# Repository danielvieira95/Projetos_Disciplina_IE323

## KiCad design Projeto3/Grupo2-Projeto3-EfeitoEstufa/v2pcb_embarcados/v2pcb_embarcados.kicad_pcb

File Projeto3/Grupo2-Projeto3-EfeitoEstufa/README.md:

# Projeto 3 - Efeito Estufa e Aquecimento Global - IE323A - Tópicos em Eletrônica

## Autor

Victor Anthony Teixeira dos Santos - 206467

## Introdução
Este projeto, se trata de um experimento em que podemos demonstrar o efeito estufa e o aquecimento global, de forma que possamos elucidar esse problema de uma maneira clara para os alunos.

## Objetivos
A ideia é que os professores possam usar a BitDogLab para complementar o que foi passado em aula, de forma que possa facilitar a melhor visualização do aluno sobre o conteúdo a ser estudado.

   Este projeto está alinhado com as seguintes habilidades específicas da BNCC:

**(EF07CI12)** Demonstrar que o ar é uma mistura de gases, identificando sua composição, e discutir fenômenos naturais ou antrópicos que podem alterar essa composição.

**(EF07CI13)** Descrever o mecanismo natural do efeito estufa, seu papel fundamental para o desenvolvimento da vida na Terra, discutir as ações humanas responsáveis pelo seu aumento artificial (queima dos combustíveis fósseis, desmatamento, queimadas etc.) e selecionar e implementar propostas para a reversão ou controle desse quadro.

## Materiais Utilizados:

**Recursos on-board**
- Display Oled
- Botão
- Matriz RGB
- Buzzer

**Recursos off-board**
- 2 x Sensores de Temperatura e Umidade BME680
- 16 x Cabos groove 20cm
- 2 x Conectores para cabo groove
- 1 x Sensor HC05
- 1 x PCB Adaptada para o sensor HC05

## Código

O software foi projetado para ter uma interação entre os sensores BME680 e o HC05, junto com o display OLED, a matriz RGB e o buzzer.
O display OLED mostrará a temperatura, umidade, gás e pressão em cada ambiente. Nessa parte tem uma interação com o botão, que ao pressionar o botão você alterna entre os sensores para ver as respectivas informações. Outra interação que vai ter é com a matriz RGB, de acordo com a temperatura a matriz RGB muda de cor e quando atingir uma temperatura acima de 30°C o buzzer aciona. Um adendo sobre a matriz RGB é que as duas primeiras colunas serão destinadas para o primeiro sensor e as duas últimas serão destinadas ao segundo sensor.
Essas informações são enviadas para o sensor bluetooth HC05, e posteriormente serão lidas por uma dashboard. Dessa forma, será possível ver as informações no celular também.

Abaixo temos dois fluxogramas do código e uma imagem para ilustrar melhor.

Fluxograma 1

Fluxograma 2

Exemplo BitDog funcionando

## PCB
Para esse projeto foi desenvolvida uma PCB, essa PCB foi utilizada para utilizar o sensor HC05, com isso, não foi preciso utilizar uma protoboard, nem deixar fio solto.
É uma PCB simples, utilizamos os pinos do conector IDC para utilizar o sensor HC05.

Listas de Materiais:

- 1 x Conector IDC Macho 2x7
- 1 x Conector Soquete Fêmea 1x4
- 1 x Led 3mm (Verde ou Vermelho)
- 1 x Resistor 150Ω
- 1 x x Cabo Flat 2x7
  
## Dashboard
A dashboard foi desenvolvida utilizando o AppInventor. O objetivo dela, é que os alunos possam ver os parâmetros dos sensores pelo celular também.

## Conexão com Bluetooth

Fazer download do AppInventor na PlayStore, após isso abrir o app, clicar em " scan QR code". Depois, é só scanear o QR Code abaixo e o app irá carregar no seu celular.

Caso o QR Code não estaja funcionando, iremos disponibilizar o arquivo .aia, dessa forma, você conseguirá não somente acessar o aplicativo, como também fazer modificações nele.

Assim que abrir o aplicativo, basta clicar em conectar, e selecionar o sensor HC05, após isso, o app começara a mostrar os parâmetros do sensor.

## Experimento

Tem como objetivo fazer uma comparação entre temperaturas em dois ambientes diferentes.

Basicamente, o experimento vai precisar de 4 garrafas pet 's, terra, planta e brita, além dos sensores de BME680 e HC05.

1 - Montar o experimento

2 - Fazer um medida antes de levar o ambiente para o sol

3 - Levar os ambientes para o sol (Recomendação: 30 minutos)

4 - Realizar outra medição após tirar o ambiente do sol

## Uso da BitDogLab

A BitDogLab possui um repositório próprio que pode ser encontrado no link:https://github.com/BitDogLab/BitDogLab/tree/main

Para uma primeira experiência com a BitDogLab

1. Energizar a placa da BitDog - Plugue o cabo USB no computador ou utilize uma bateria adequada.
2. Aguarde enquanto a BitDog realiza o seu proceso de inicialização automático.
3. Abrir a IDE Thonny e carregar os códigos que estão no repositório
 
**Observações importantes**

Caso for replicar o experimento, não esquecer de:
- Carregar a biblioteca BME680 no microcontrolador.
- Ficar atento quando for utilizar os pinos da comunicação I2C.
- Ficar atento ao ligar os pinos do I2C com os pinos do sensor BME680.
- Ficar atento para conectar corretamente os sensores, lembrando que o I2C1 fica na esquerda da BitDogLab e o I20 fica na direita.
- Em relação ao sensor HC05, não esquecer que ele é alimentado com 5V e a ligação dele é TX - RX e RX- TX.

Para mais informações consultar o documento no docs, lá tem uma explicação detalhada do código e do experimento.

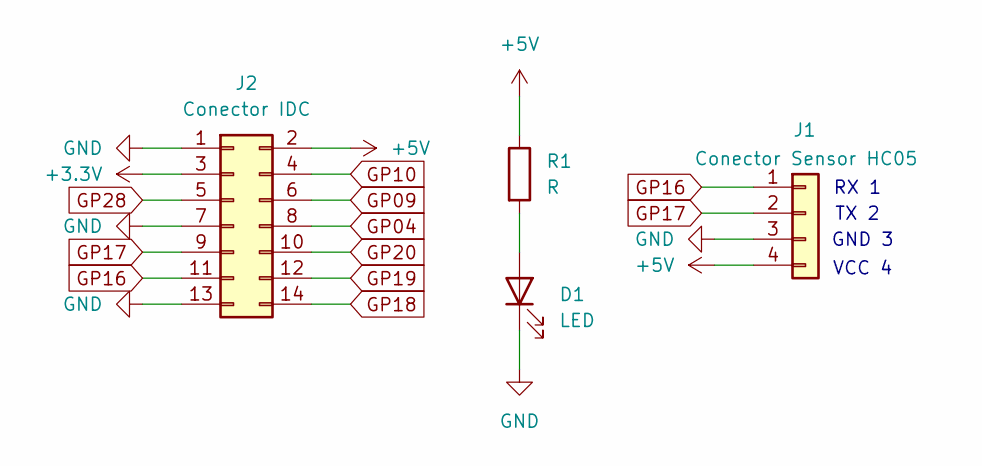
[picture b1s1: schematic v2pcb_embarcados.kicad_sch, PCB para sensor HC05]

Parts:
D1: LED; LED_D3.0mm
J1: Conector Sensor HC05; PinSocket_1x04_P2.54mm_Vertical
J2: Conector IDC; PinHeader_2x07_P2.54mm_Vertical
R1: R; R_Axial_DIN0207_L6.3mm_D2.5mm_P10.16mm_Horizontal

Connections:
+3.3V: J2.3
+5V: J1.4, J2.2, R1.1
GND: D1.1 (K), J1.3, J2.1, J2.7, J2.13
GP04: J2.8
GP09: J2.6
GP10: J2.4
GP16: J1.1, J2.11
GP17: J1.2, J2.9
GP18: J2.14
GP19: J2.12
GP20: J2.10
GP28: J2.5
unnamed: D1.2 (A), R1.2

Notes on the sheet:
RX 1
GND 3
VCC 4
TX 2

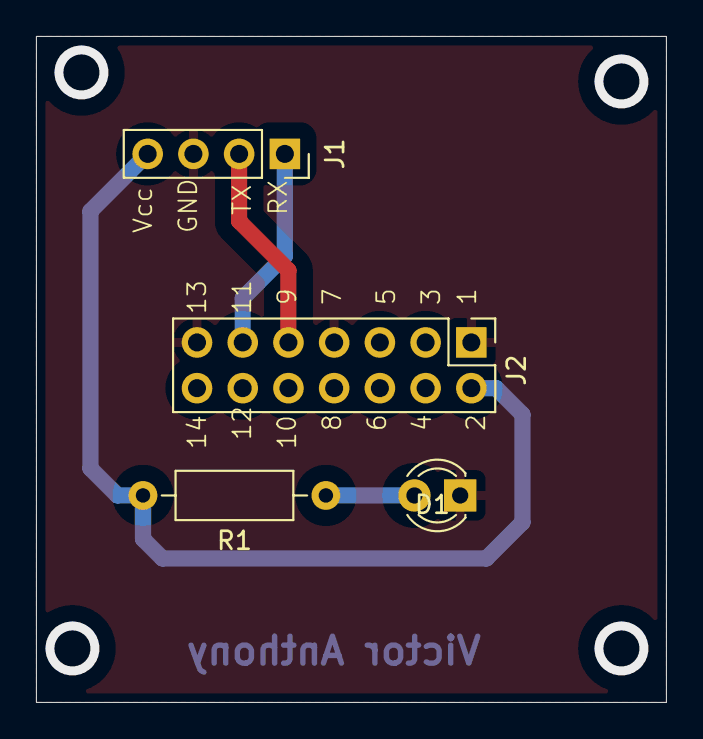
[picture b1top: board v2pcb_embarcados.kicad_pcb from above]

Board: 2 copper layers, 35.0 x 37.0 mm, 4 parts (0 on the bottom side), 5 nets.

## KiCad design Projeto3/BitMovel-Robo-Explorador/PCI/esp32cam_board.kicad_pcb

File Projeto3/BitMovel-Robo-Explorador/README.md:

# Robô explorador

Esse repositório contém o Projeto 3 do Grupo 5 da matéria de IE323 - Tópicos em Eletrônica, da Faculdade de Engenharia Elétrica e de Computação da Universidade Estadual de Campinas.

O trabalho, como projeto educacional, busca apresentar para estudantes uma ideia para criação de robôs através da união de conceitos como comunicação sem fio, utilizando Bluetooth e Wi-Fi, sinais modulados por largura de pulso (PWM) para controle de motores, lógica para movimentação de robôs, uso de sensores para exploração e percepção do ambiente, como câmera, sensor de temperatura e sensor ultrassônico, movimentação e criação de um aplicativo de celular. O projeto é um compilado de sugestões de atividades didáticas, contendo exposição teórica em slides e também exemplos práticos utilizando a placa [BitDogLab](https://github.com/BitDogLab/BitDogLab/tree/main) e periféricos listados a seguir.

Os alunos irão interagir com o robô através de um **aplicativo de celular** que controla a movimentação do agente robótico por meio do movimento do aparelho. Para isso, é utilizado o **acelerômetro**, um sensor interno que serve como fonte de dados da movimentação que está sendo realizada. Ao identificar a direção do deslocamento através da análise desses dados, é enviado um comando à BitDogLab via **Bluetooth**, que será interpretado e executado pela placa. Também utilizando o Bluetooth, é possível enviar **dados de temperatura e umidade** de um sensor conectado à BitDogLab para exibição no aplicativo. Ainda, o aplicativo apresenta, em tempo real, **imagens** que estão sendo enviadas por **wi-fi** para um servidor web por uma câmera disposta no agente robótico, sendo possível movimentar a câmera por meio de um **joystick** disposto no aplicativo de celular, que controla dois servo motores presentes no robô que servem como base para a câmera. Caso o robô esteja muito próximo de um obstáculo, um **sensor ultrassônico** irá detectar e impedir movimentos frontais, evitando a possível colisão.

### Autores

Carlos Julián Muñoz Quiroga, RA: 204200  
Patric Moreto, RA: 223083

## Recursos de hardware utilizados da BitDogLab

**On-board:**
- Buzzer
- Matriz de LEDs 5 x 5
- Periférico para comunicação UART/I2C (canais 0 e 1)

**Off-board:**
- Celular
- Módulo bluetooth HC-05
- Robô móvel ([chassi](https://www.tinkercad.com/things/1lvaPDfdjkt-chassi-bitmovel/edit?sharecode=c4YGIVprehL-UuPeUL_7wFy6jiYbiTO2cclIelt4kQc), [aerofólio](https://www.tinkercad.com/things/buQTXUUQPVn-aerofolio/edit?returnTo=%2Fthings%2FbuQTXUUQPVn-aerofolio) e [conexões + detalhes](https://docs.google.com/document/d/19eDUn6APOkDckY-d9zxlf_N0l-tGTjby_PLXqS_WKOg/edit?usp=sharing))
- 2 motores DC
- 2 rodas 68 mm
- Bateria LiPo 2S 550 mAh
- Driver para motor (ponte H TB6612FNG)
- ESP32-CAM + OV2640
- Módulo conversor USB / TTL
- Sensor ultrassônico HC-SR04
- Sensor de temperatura AHT10
- Placa de circuito impresso
- 2 servo motores + suporte plástico/impresso em 3D para movimentação pan e tilt
- Placa expansora com expansão I2C e regulador 5 V

Os componentes que podem ser comprados facilmente estão tabelados a seguir.

|             Item             | Quantidade |                        Descrição                        | Código de fabricante  | Links |
|:----------------------------:|:----------:|:-------------------------------------------------------:|:---------------------:|:-----:|
|             HC-05            |      1     |                     Módulo Bluetooth                    |         HC05          |  [Link](https://www.a2robotics.com.br/produto/modulo-bluetooth-hc-05.html?utm_source=Site&utm_medium=GoogleShopping&utm_campaign=IntegracaoGoogle&gad_source=1&gclid=Cj0KCQjw0Oq2BhCCARIsAA5hubX2GjhASd7V3xTfM1GVxpMPHIr0fWWGYT2esOJLsDMWn-IL-hZoXdQaArUfEALw_wcB) |
|       JST fêmea 4 pinos      |      2     |           Conector JST fêmea 4 pinos com cabo           |         2CB96         |  [Link](https://www.makerhero.com/produto/conector-jst-4-pinos-femea/) |
|           ESP32-CAM          |      1     |             Módulo ESP32-CAM + câmera OV2640            |         6WL90         |  [Link](https://www.makerhero.com/produto/modulo-esp32-cam-com-camera-ov2640-2mp/) |
|     Módulo gravador CH340    |      1     | Módulo gravador conversor USB/Serial CH340 para ESP-CAM |         GC09          |  [Link](https://www.casadarobotica.com/placas-embarcadas/esp/shield/modulo-conversor-shield-usb-serial-ch340-para-esp32-cam-esp32) |
| Conversor USB Serial FT232RL |      1     |           Módulo conversor USB/Serial FT232RL           |       N9EK77PXR       |  [Link](https://www.a2robotics.com.br/conversor-usb-serial-ft232rl-ft232?utm_source=Site&utm_medium=GoogleShopping&utm_campaign=IntegracaoGoogle&gad_source=1&gclid=CjwKCAiAjKu6BhAMEiwAx4UsAobkDi_B8SoBQAFprDd8rf7sh3_WokTIa423_h0s4shOevF-Tbq56hoCV2gQAvD_BwE) |
|            HC-SR04           |      1     |         Sensor de distância ultrassônico HC-SR04        |         9SS01         |  [Link](https://www.makerhero.com/produto/sensor-de-distancia-ultrassonico-hc-sr04/) |
|             AHT10            |      1     |          Sensor de temperatura e umidade AHT10          |         08807         |  [Link](https://www.usinainfo.com.br/sensor-de-temperatura/sensor-aht10-de-alta-precisao-para-medir-temperatura-e-umidade-5691.html) |
|       Suporte pan/tilt       |      1     |      Suporte movimentação pan/tilt de servo motores     |        C15-001        |  [Link](https://www.eletrogate.com/suporte-pan-tilt-para-servo-motor) |
|          Servo motor         |      2     |              Servo motor SG90 9g Tower Pro              |         7MS09         |  [Link](https://www.makerhero.com/produto/micro-servo-9g-sg90-towerpro/) |
|          XT30 fêmea          |      2     |                   Conector XT30 fêmea                   |         UC02          |  [Link](https://www.casadarobotica.com/ver-mais/conector-xt-30-femea-conector-lipo?parceiro=3259&gad_source=1&gclid=CjwKCAiAjKu6BhAMEiwAx4UsAraRZJcCj56NbO9tpxZhVxdyxqlVdJuIaMfyusyq7Y3sOVDGIc3oGBoCwFMQAvD_BwE) |
|          XT30 macho          |      1     |                   Conector XT30 macho                   |         UC01          |  [Link](https://www.casadarobotica.com/ver-mais/conector-xt-30-macho-conector-lipo?parceiro=3259&gad_source=1&gclid=CjwKCAiAjKu6BhAMEiwAx4UsArPk5ABlAASJx575vaAB5vW-nAvS3B6FmgVn1CDUrXsmXweUmmXCAhoC5yQQAvD_BwE) |
|            LiPO 2S           |      1     |           Bateria Lipo 2S GNB HV 550 mAh 100c           |       3N9CS8V6D       |  [Link](https://www.mercadofpv.com.br/bateria-lipo-2s-gnb-550mah-xt30-100c-76v?srsltid=AfmBOoq2uLk96ERSVQooedK1l6WyxYJDRnEFS2iBRDe8iuiaUZJb9Uuk) |
|       Driver TB6612FNG       |      1     |                 Driver TB6612FNG Ponte H                |         07766         |  [Link](https://www.usinainfo.com.br/driver-para-motor/driver-tb6612fng-duplo-ponte-h-de-motor-dc-ou-passo-4697.html) |
|           Motor DC           |      2     |     Motor DC 3-6V com Caixa de Redução e Eixo Duplo     |       DG01D-A130      |  [Link](https://www.robocore.net/motor-motoredutor/motor-dc-3-6v-com-caixa-de-reducao-e-eixo-duplo?srsltid=AfmBOoqLHgizbn0gZF61xttOR3IJUD1AubocqiVNkSUDRpU2Qb-1_WqD) |
|          Roda 68 mm          |      2     |                        Roda 68 mm                       |       B2-CP-001       |  [Link](https://www.eletrogate.com/roda-68mm-para-chassi-robo-robotica) |
|         Expansor I2C         |      1     |      Placa de expansão I2C (entregue pelo professor)    |                       |  [Link]() |
|         Regulador 5 V        |      1     |      Regulador De Tensão Ams1117 5V                     |      Ams1117-5.0      |  [Link](https://produto.mercadolivre.com.br/MLB-3645845877-10x-regulador-de-tenso-ams1117-smd-12v-15v-18v-33v-_JM?attributes=Vm9sdGFnZW0=:NXY=) |
|       Borne KRE 2 vias       |      1     |                Conector borne KRE 2 vias                |       CCHGW3DTS       |  [Link](https://www.a2robotics.com.br/conector-borne-kre-2-vias?utm_source=Site&utm_medium=GoogleShopping&utm_campaign=IntegracaoGoogle&gad_source=1&gclid=CjwKCAiAjKu6BhAMEiwAx4UsAmFMy1QJVd-eJWjm5CC3EwINnCmLZXtyfIS3I62MyXeWaU2be4_r1BoCVmMQAvD_BwE) |
|             Cabos            |      1     |             Kit com 40 cabos (usos diversos)            |  3CKD45VR8-9APYHNRP1  |  [Link](https://www.a2robotics.com.br/9apyhnrp1-jumper-femea-x-femea-20-cm-c-40-cabos) |

## Placa de circuito impresso

Foi criada uma PCI que possibilita o carregamento de programas na ESP32-CAM sem a necessidade de remover o módulo do BitMóvel, sendo apenas necessário inserir um jumper e alimentar a placa. O projeto da placa foi feito no Kicad está disponível na pasta PCI, sendo possível visualizar sua prévia abaixo.

Caso deseja-se realizar as ligações da ESP32-CAM com o conversor USB / TTL sem utilizar a PCI, as ligações e o esquemático a seguir devem ser seguidos, sendo necessária alimentação externa nos pinos de 5 V e GND.

| ESP32-CAM | USB / TTL |
|-----------|-----------|
| 5V        | 5V        |
| GND       | GND       |
| U0T       | RX (RXC)  |
| U0R       | TX (TXD)  |

## Fluxogramas

### Diagrama de blocos de hardware

### Software na BitDogLab

### Software na ESP32-CAM

### Aplicativo de celular

## Instruções de uso do aplicativo + robô

- **Instalação do aplicativo:** O aplicativo feito no MIT App Inventor é para celulares Android. Sua instalação é simples, basta ler o QR Code abaixo e o usuário será direcionado para o download do arquivo em formato APK. Normalmente, após o download for concluído, aparecerá a opção de abrir o arquivo com a opção do instalador do celular. Caso não, procure pelo arquivo *bitmovel_explorador.apk* em sua pasta de Downloads, clique nele e escolha o instalador. É bem provável que você tenha que permitir manualmente a instalação do aplicativo.
<br/><br/>

- **Aplicativo:** Abra o aplicativo recém instalado, procurando por *BitMóvel Explorador*. O aplicativo funciona apenas com o celular na horizontal. O símbolo Bluetooth em cinza no canto superior esquerdo indica que ainda não foi feita a conexão com o módulo Bluetooth instalado no veículo, mais detalhes serão explicados no tópico seguinte. O símbolo de uma buzina no canto superior direito é um botão, que fará o robô emitir um som enquanto estiver pressionado. No canto inferior esquerdo há um espaço que apresenta dados de temperatura e pressão do sensor de temperatura AHT10, como uma versão simplificada do [Projeto 3 de efeito estufa](https://github.com/danielvieira95/Projetos_Disciplina_IE323/tree/main/Projeto3/Grupo2-Projeto3-EfeitoEstufa). Há um joystick azul no canto inferior direito que serve para controlar os servo motores da posição da câmera. Os retângulos em branco indicam quais os possíveis movimentos a serem enviados ao robô, enquanto o retângulo em azul indica qual é a direção que está sendo enviada nesse momento. Caso todos os retângulos estejam em branco, está sendo executado o comando de ficar parado.    
Existem 5 movimentos padrões, que são avançar, virar para a esquerda, virar para a direita, retroceder e ficar parado, além das combinações avançar para esquerda, avançar para a direita, retroceder para a esquerda e retroceder para a direita.    
No centro da tela, caso o celular esteja conectado no wi-fi do robô, são exibidas as imagens capturadas pela câmera da ESP32-CAM. É possível dar zoom na imagem fazendo o movimento de pinça com os dedos.

- **Conexão Bluetooth:** No aerofólio do robô, conecte o jumper que vem com o robô entre o pino central e o pino da direita (olhando para o robô de frente) para habilitar a alimentação de 5V para todo o robô, incluindo o módulo bluetooth, que indicará que está energizado piscando rapidamente um LED vermelho. A figura a seguir apresenta a posição do jumper mencionado.    

Antes de pressionar o botão de Bluetooth no aplicativo, é necessário conectar previamente o celular ao Bluetooth do robô uma primeira vez. Procure por *HC-05* entre os dispositivos disponíveis em seu celular e conecte-se utilizando a senha *1234*.    
Voltando para o aplicativo, ao pressionar o botão de Bluetooth será aberta uma lista de dispositivos que você já se conectou previamente, basta selecionar o HC-05. É normal que ocorra uma pequena demora, então será aberta a tela inicial novamente, mas agora o símbolo do Bluetooth estará azul, indicando a tentativa de conexão Bluetooth com o robô. O módulo HC-05 irá piscar seu LED vermelho lentamente quando a conexão for bem sucedida. Caso a conexão falhe ou seja perdida por alguma razão, feche o aplicativo e tente conectar novamente clicando no botão do Bluetooth (agora em cinza novamente).

- **Conexão Wi-Fi:** Ao ligar o robô, a placa ESP32-CAM será energizada e iniciar seu access point. Basta conectar o celular à rede wi-fi *BitMovel-WiFi* e as imagens da câmera estarão disponíveis no aplicativo.

- **Gravação de código na ESP32-CAM:** Para gravar um novo código na ESP32-CAM, na PCI que acompanha o robô, há uma placa vermelha ao lado da câmera dedicada para isso. Coloque o jumper utilizado na etapa de Conexão Bluetooth, de maneira a conectar os dois pinos macho separados no canto esquerdo inferior da placa, conforme indicado na imagem abaixo, e conecte o cabo mini USB à placa vermelha. Isso fará a ESP32-CAM entrar em modo de gravação. Agora basta abrir o Arduino IDE e carregar o novo programa desejado.

- **Robô:** Confira se as rodas estão bem encaixadas e que não estão em contato com o parafuso, podendo causar travamento das rodas. Caso esteja tudo bem e o jumper já esteja conectado conforme instruções da seção Conexão Bluetooth, basta apertar o botão *LIGA/DESLIGA* na placa BitDogLab, que está no canto esquerdo superior, olhando para o robô de cima e com as rodas para o lado de baixo, de acordo com o destacado na figura a seguir. Para desligar o veículo, basta apertar duas vezes o mesmo botão.

## Projeto do aplicativo feito no MIT App Inventor

O arquivo *bluetooth_explorador.aia* disponibilizado nesse repositório contém o projeto do aplicativo de celular desenvolvido. É possível fazer o download desse projeto e importar para o MIT App Inventor, sendo possível realizar edições, ou baixar o arquivo .apk diretamente do repositório ou pelo QR Code acima.

## Resultados

### Robô explorador construído a partir da BitDogLab:

### Aplicativo de celular do projeto:

- Entre os pontos positivos, destaca-se a possibilidade de abordar diversos temas que envolvem a robótica com os alunos em sala de aula, seja sensores e seus funcionamentos (como o sensor ultrassônico), microcontroladores, lógica de programação, comunicação, aplicativos, processamento descentralizado e outros. Por ser um robô/carrinho, o visual pode ser um facilitador para atrair o interesse e curiosidade dos alunos.

- Outro ponto a ser mencionado é a oportunidade de exercitar diferentes tecnologias, como microcontroladores e linguagens de programação, a criação de aplicativo, envolvendo programação em blocos e design, a criação de uma placa de circuito impresso, comunicação Wi-Fi e Bluetooth e a integração de toda essa diversidade, permitindo interação entre elas, como o aplicativo recebendo dados da ESP32 e da Raspberry Pi Pico e enviando dados para a Pico simultaneamente, sendo necessário tratar de possíveis concorrências. É uma solução completa e que possui áreas distintas para todos os interesses.

- Uma dificuldade observada durante toda a disciplina é desenvolver atividades e projetos que sejam acessíveis e interessantes para alunos, com instruções e objetivos claros para os professores em sala de aula utilizarem como uma ferramenta facilitadora e engajante, ao mesmo tempo que seja possível abstrair todos os desafios técnicos dos desenvolvedores, criando uma solução robusta o suficiente para o ambiente de uma sala de aula. Como exemplo, manusear o robô, ligando e desligando em caso de problemas, pode apresentar dificuldade inicialmente, mesmo com os manuais simplificados contendo imagens.

- Um ponto negativo observado ao fim da etapa de desenvolvimento foi o tempo de duração da bateria. Com a adição da ESP32-CAM e novos sensores, o robô possui um intervalo de funcionamento curto, que não permite muita flexibilidade em sala de aula. Faz-se necessária a ampliação da capacidade da bateria atual e é recomendado a integração com o sistema de monitoramento de carga do BitMóvel Seguidor de Linha por segurança, dado que a descarga total de uma bateria LiPo é perigosa.

## Possíveis mudanças para o futuro

- Substituição de bateria LiPo por uma de maior capacidade (maior que 550 mAh). É possível que seja necessário mudar os conectores XT30 e a localização da bateria por causa do maior tamanho.
- Por questões de segurança ao utilizar uma bateria LiPo, recomenda-se uma forma de monitorar sua carga. Exitem [módulos tradicionalmente utilizados](https://www.robocore.net/sensor-corrente-tensao/monitor-de-tensao-para-baterias-1s-8s?gad_source=1&gclid=CjwKCAiAjKu6BhAMEiwAx4UsArDSI4isRYA_fTmwPpj56Cw4_OTkpDHh7RrQrH3L0IJNwP9G7HvslRoC8WsQAvD_BwE) que dispõe de alarme embutido, mas recomenda-se a solução open-source feita para o [BitMóvel Seguidor de Linha](https://github.com/danielvieira95/Projetos_Disciplina_IE323/tree/main/Projeto3/Grupo3-BitMovel-Seguidor-de-Linha), que permite acompanhar o estado da bateria por aplicativo de celular.

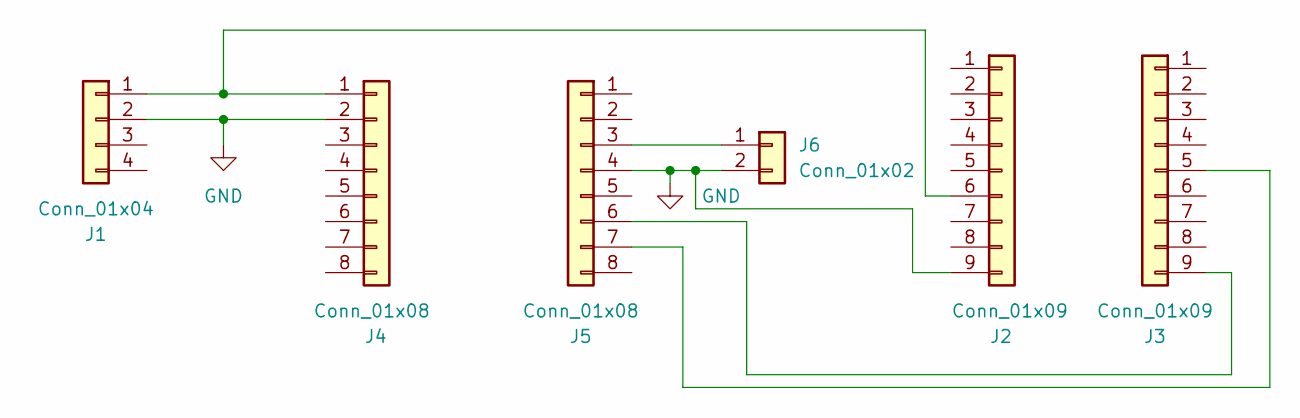
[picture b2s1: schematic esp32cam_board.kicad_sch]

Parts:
J1: Conn_01x04; Molex_KK-254_AE-6410-04A_1x04_P2.54mm_Vertical
J2, J3: Conn_01x09; PinSocket_1x09_P2.54mm_Vertical
J4, J5: Conn_01x08; PinSocket_1x08_P2.54mm_Vertical
J6: Conn_01x02; PinHeader_1x02_P2.54mm_Vertical

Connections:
GND: J1.2, J2.9, J4.2, J5.4, J6.2
unnamed: J1.1, J2.6, J4.1
unnamed: J3.5, J5.7
unnamed: J3.9, J5.6
unnamed: J5.3, J6.1

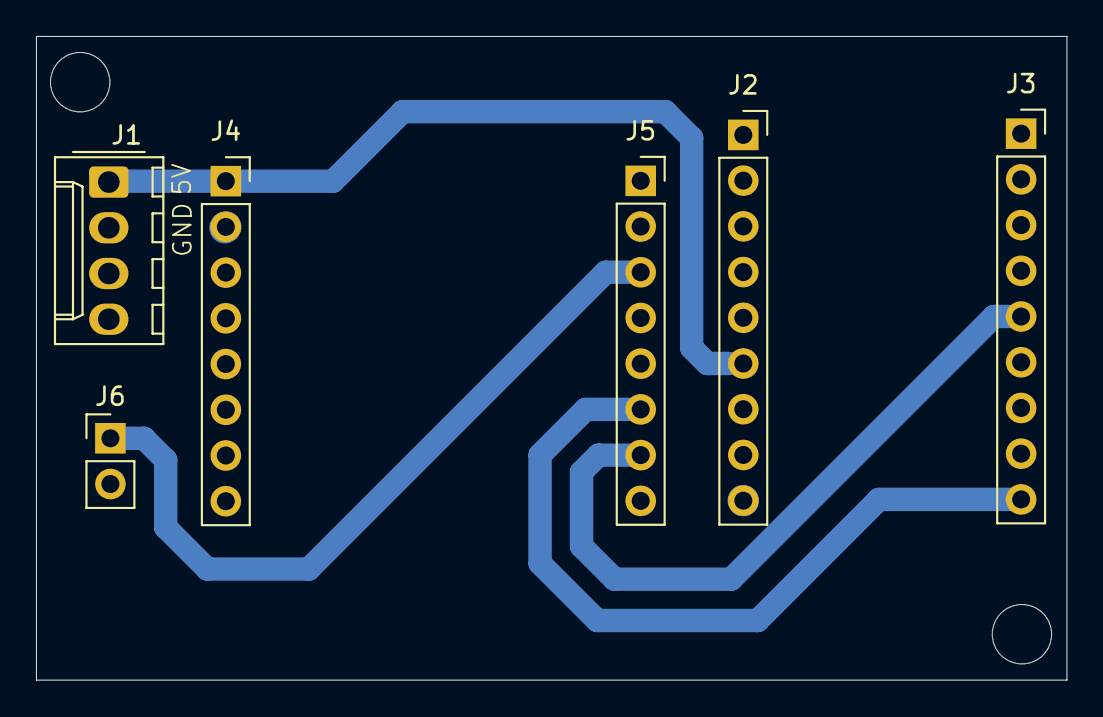
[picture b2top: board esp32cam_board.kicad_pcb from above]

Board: 2 copper layers, 57.2 x 35.8 mm, 6 parts (0 on the bottom side), 5 nets.

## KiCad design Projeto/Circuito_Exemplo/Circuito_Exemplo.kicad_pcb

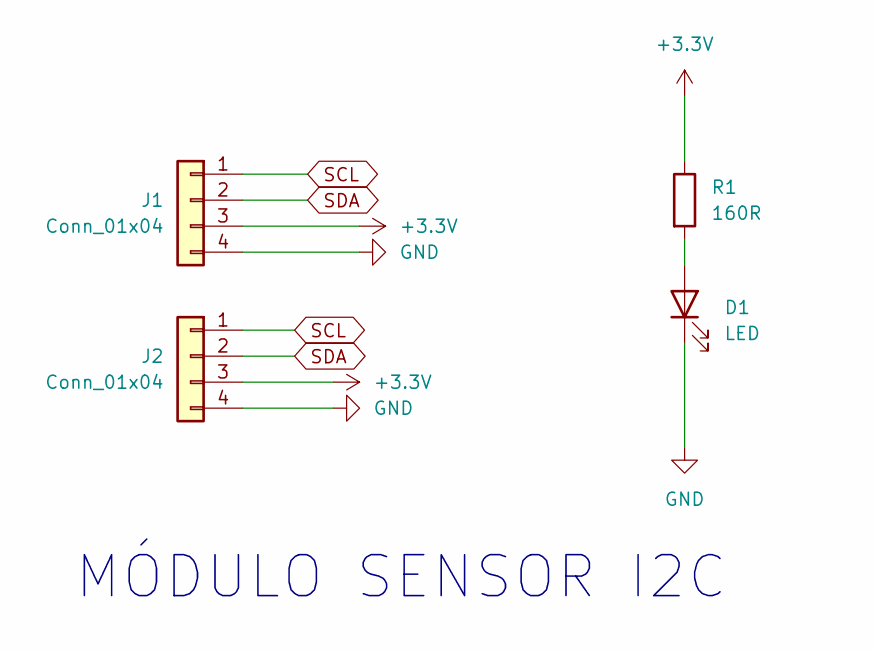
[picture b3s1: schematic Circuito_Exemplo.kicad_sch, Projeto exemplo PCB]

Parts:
D1: LED; LED_D5.0mm
J1: Conn_01x04; PinSocket_1x04_P2.54mm_Vertical
J2: Conn_01x04; Molex_KK-254_AE-6410-04A_1x04_P2.54mm_Vertical
R1: 160R; R_Axial_DIN0207_L6.3mm_D2.5mm_P10.16mm_Horizontal

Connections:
+3.3V: J1.3, J2.3, R1.1
GND: D1.1 (K), J1.4, J2.4
unnamed: D1.2 (A), R1.2
SCL: J1.1, J2.1
SDA: J1.2, J2.2

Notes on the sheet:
MÓDULO SENSOR I2C

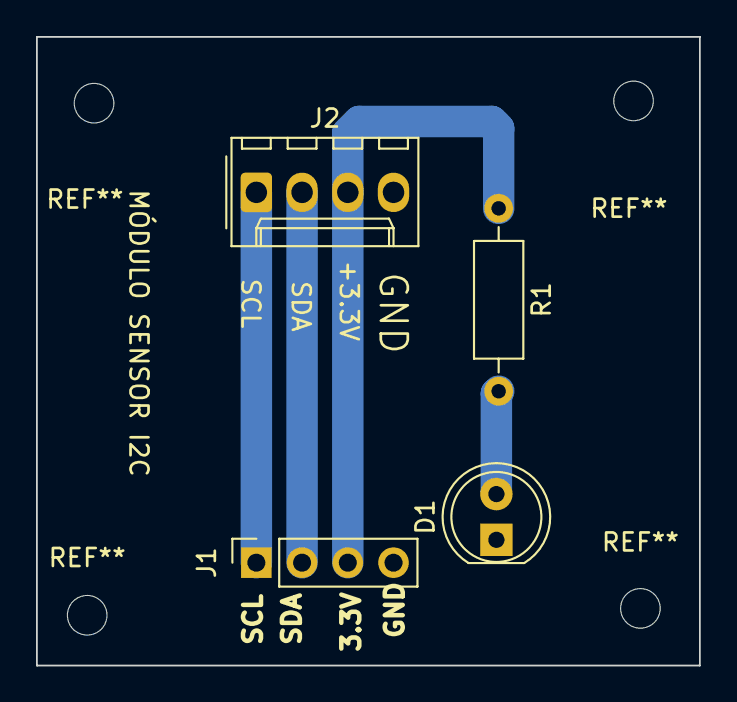
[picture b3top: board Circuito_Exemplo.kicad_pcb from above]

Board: 2 copper layers, 36.8 x 34.9 mm, 4 parts (0 on the bottom side), 5 nets.

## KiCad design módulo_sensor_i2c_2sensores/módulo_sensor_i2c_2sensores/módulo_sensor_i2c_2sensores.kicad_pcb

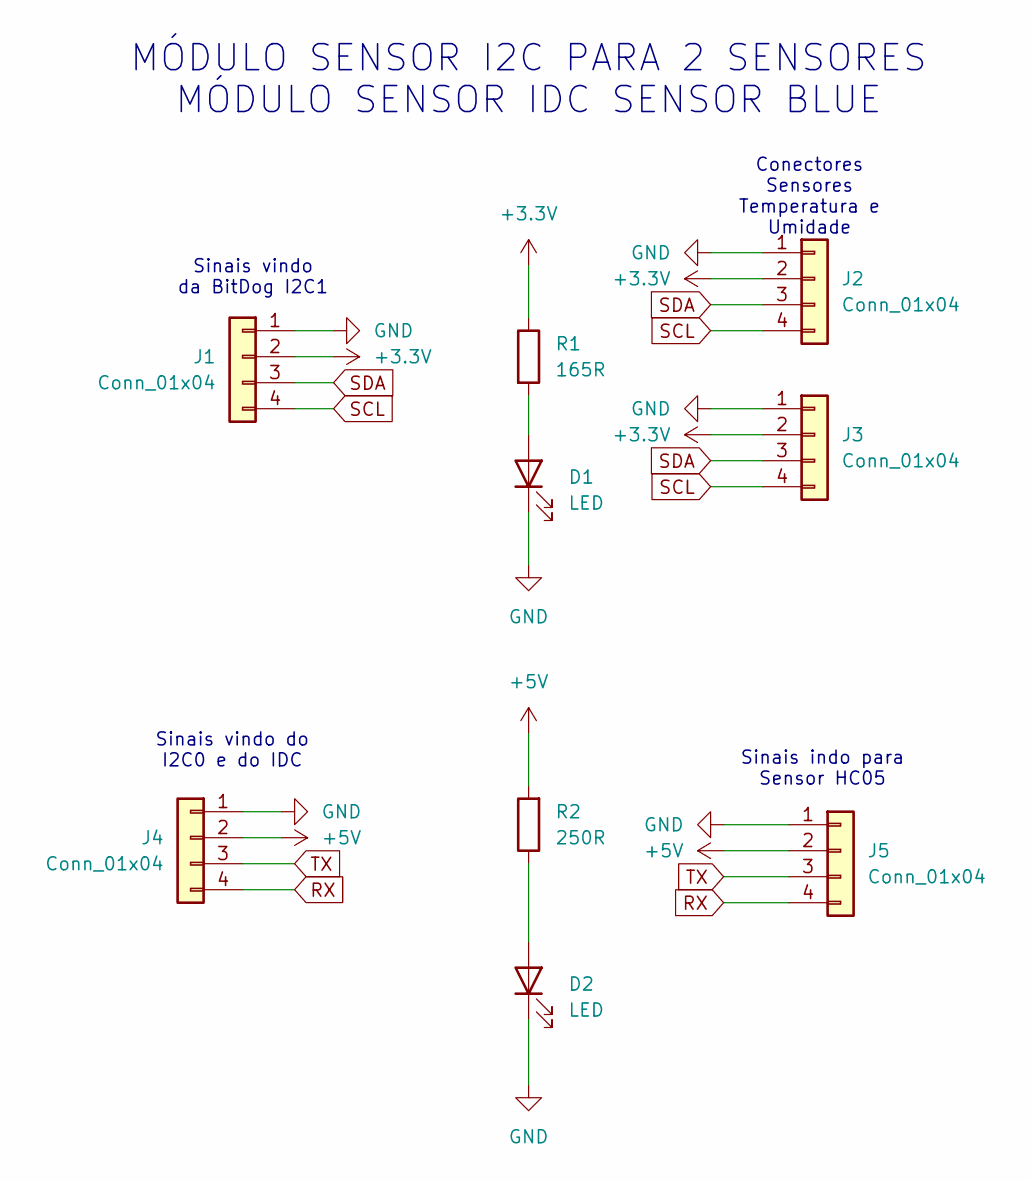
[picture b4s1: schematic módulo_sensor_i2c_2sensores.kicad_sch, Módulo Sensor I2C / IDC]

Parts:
D1, D2: LED; LED_D3.0mm
J1, J2, J3, J4, J5: Conn_01x04; JST_XH_B4B-XH-A_1x04_P2.50mm_Vertical
R1: 165R; R_Axial_DIN0207_L6.3mm_D2.5mm_P10.16mm_Horizontal
R2: 250R; R_Axial_DIN0207_L6.3mm_D2.5mm_P10.16mm_Horizontal

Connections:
+3.3V: J1.2, J2.2, J3.2, R1.1
+5V: J4.2, J5.2, R2.2
GND: D1.1 (K), D2.1 (K), J1.1, J2.1, J3.1, J4.1, J5.1
unnamed: D1.2 (A), R1.2
unnamed: D2.2 (A), R2.1
RX: J4.4, J5.4
SCL: J1.4, J2.4, J3.4
SDA: J1.3, J2.3, J3.3
TX: J4.3, J5.3

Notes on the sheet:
Sinais indo para Sensor HC05
MÓDULO SENSOR I2C PARA 2 SENSORES MÓDULO SENSOR IDC SENSOR BLUE
Sinais vindo da BitDog I2C1
Conectores Sensores Temperatura e Umidade
Sinais vindo do I2C0 e do IDC

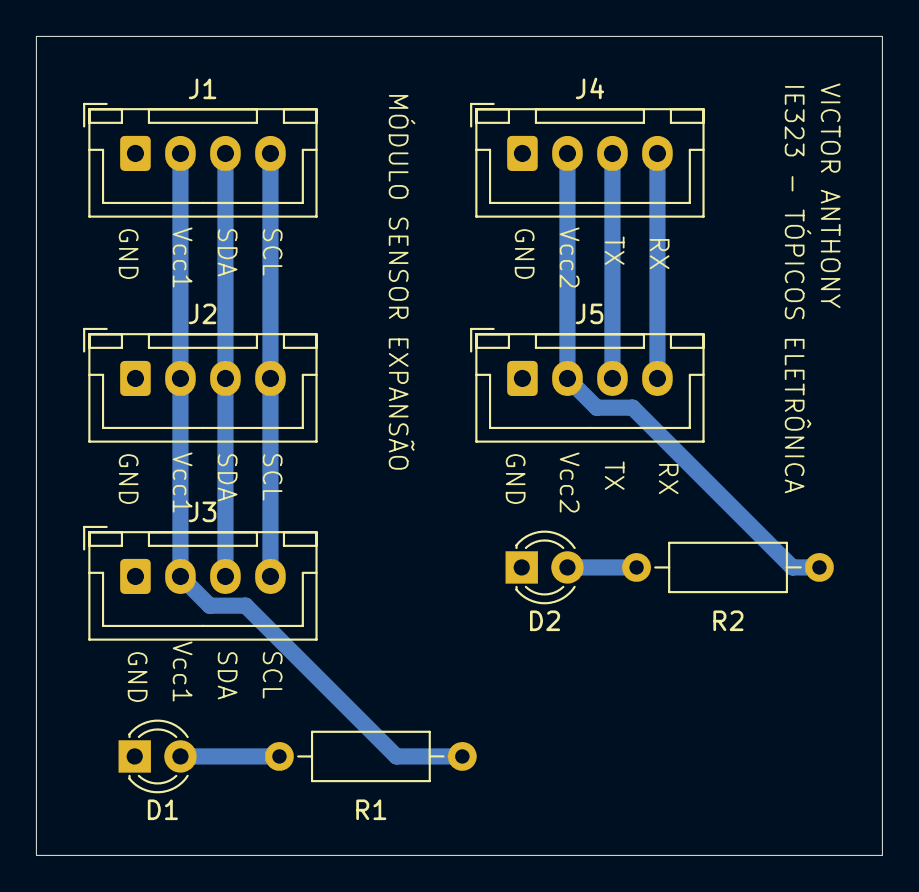
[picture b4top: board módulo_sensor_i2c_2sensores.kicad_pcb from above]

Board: 2 copper layers, 47.0 x 45.5 mm, 9 parts (0 on the bottom side), 9 nets.

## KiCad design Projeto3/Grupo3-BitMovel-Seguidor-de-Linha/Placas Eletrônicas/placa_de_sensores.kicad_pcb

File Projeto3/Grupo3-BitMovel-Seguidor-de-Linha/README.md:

# BitMóvel Seguidor de Linha, versao com monitoramento de bateria
## Autores
Edson Costa Oliveira, RA: 188405 <br>
Vinicius Emanoel Ares, RA: 083028

<div align="center">

</div>

<div align="center">

</div>

<br><br>
BitMóvel Seguidor de Linha é um projeto educacional de robô seguidor de linha para a placa [BitDogLab](https://github.com/BitDogLab/BitDogLab). O projeto foi desenvolvido como projeto 3 da disciplina da FEEC/Unicamp IE323 - Sistemas Embarcados para ensino com abordagem STEM
<details>
  <summary>Clique para saber mais sobre a disciplina.</summary>
  Sistemas Embarcados para ensino com abordagem STEM é uma disciplina da pós-graduação da FEEC-UNICAMP ofertada pelo professor Fabiano Fruett com auxílio do professor Daniel Vieira. O objetivo da matéria é desenvolver projetos que envolva IoT, eletrônica e IA com o intuito de levar ferramentas para os alunos do ensino fundamental e médio utilizando a abordagem STEM (Science, Technology, Engineering and Mathematics). [BitDogLab](https://cpg.fee.unicamp.br/lista/caderno_horario_show.php?id=1932).
</details>
O objetivo do Projeto 3 da disciplina é utilizar a placa BitDogLab conectada a dispositivos externos, com a proposta de preparar o projeto para uso em escolas. Isso inclui a inclusão de mecanismo de ajuste da altura dos sensores com 3 parafusos, e o desenvolvimento de placas eletrônicas para reduzir a necessidade de fios (jumpers).<br><br>

<div align="center">

</div>

O BitMóvel Seguidor de Linha é um robô diferencial com 2 rodas motrizes e uma esfera de apoio na frente, formando um tripé ou triciclo. O robô usa sensores reflexivos infravermelhos QRD1114 para detectar uma linha escura no chão. O design do carrinho é fabricado por impressão 3D em PLA. Além da função seguidor de linha, os botões A e B são programados para comandar o robô para ativo ou desativado, respectivamente. O robô inicia no modo desativado, então quando o botão A é pressionado o robô está em modo de movimento ativo para frente seguindo a linha embaixo do chassis. Quando o botão B é pressionado o robô fica parado até que se pressione o botão A novamente. O BitMóvel conta com um aplicativo que permite o monitoramento da bateria. Por meio dele, o usuário pode acessar informações sobre o BitDogLab, controlar o acionamento e desligamento do carrinho, verificar o nível da bateria e obter suporte técnico. Além disso, o código implementado protege o carrinho contra níveis críticos de bateria e situações de sobrecorrente no circuito.

### Lista de Componentes
- 2 motores DC 3-6V com Caixa de Redução e Eixo Duplo + Roda 68mm
- 1 Driver ponte H modelo HW-166
- 1 bateria 2s1p 7,6V 550mAh
- 1 placa de sensores conforme arquivo (Projeto3/Grupo3-BitMovel-Seguidor-de-Linha/Placas Eletrônicas/placa_de_sensores.kicad_pcb)
- 1 módulo ADS1115
- 1 placa de monitoramento de bateria conforme arquivo (Projeto3/Grupo3-BitMovel-Seguidor-de-Linha/Placas Eletrônicas/monitoramento.kicad_pcb)
- 1 módulo Bluetooth HC-05
- 1 módulo INA-226
- 1 placa expansor I2C conforme arquivo (Projeto3/Grupo3-BitMovel-Seguidor-de-Linha/Placas Eletrônicas/expansão_i2c.kicad_pcb)
- Peças para impressão 3D conforme arquivo (desenhos_mecanicos_3d/suporte_sensores_avulsos.STL)
- 3 parafusos M3 30mm
- 6 porcas m3
- Fita isolante
- fita dupla-face
<br><br>

O fluxograma abaixo ilustra o funcionamento do programa embarcado no microcontrolador da BitDogLab:

<div align="center">

</div>

O fluxograma abaixo ilustra o funcionamento do aplicativo de celular:

<div align="center">

</div>

Para mais informações, é possível acessar o relatório do projeto disponibilizado no [link](https://docs.google.com/document/d/1KMj3I93LfhJuYwX31ApxWePKK1TJ1PmV/edit?usp=sharing&ouid=113991507111012118869&rtpof=true&sd=true).

## Como instalar e operar o robô físico?

1. Instale a IDE Arduino.
2. Conecte a placa BitDogLab ao computador através de um cabo micro-USB.
3. Para utilizar a Raspberry Pi Pico, é necessário instalar o gerenciador de porta Raspberry Pi Pico RP2040. Vá em `File > Preferências` e copie `https://github.com/earlephilhower/arduino-pico/releases/download/global/package_rp2040_index.json` em `Additional Boards manager URL's`. Em seguida, vá em `Tools > Board > Board manager`e instale `Raspberry Pi Pico/RP2040 by Earlephilhower`.
4. Baixe os códigos `Projeto_Seguidor_de_Linha.ino` neste repositório.
5. Na IDE Arduino, acesse `Arquivo > Abrir` e localize o arquivo `Projeto_Seguidor_de_Linha.ino` (por exemplo, na pasta Downloads).
6. Pressione o botão de verificar o código para certificar-se que não há erro, caso esteja tudo certo:
7. Pressione o botão "carregar" (setinha) para carregar o código para a placa, esta operação salva e executa o código em uma única etapa.
8. Pronto, você pode desconectar a BitDogLab e o programa pode ser executado (ou reiniciado) apertando o botão próximo à bateria.

## Como conectar o Bluetooth do App com o carrinho? 

1. Instale o app BitMovel.apk
2. Clique em "BitDogMovel Bluetooth".
3. Certifique-se de que o Bluetooth do celular está ativado.
4. Clique em Dispositivos.
5. Procure na lista "HC-05" e clique. O status do carrinho exibirá "conectado".
6. Caso ocorra algum erro de conexão, repita o processo a partir do 4.

## Fabricação e montagem do projeto
1. Para fabricação das placas de circuito impresso, devem ser encomentadas de um fabricantes como JLCPCB ou outro de sua preferência, projetos disponíveis na pasta Placas Eletrônicas.
2. Usar uma impressora 3D para imprimir as partes disponíveis na pasta desenhos_3D.
3. Adquirir os materiais descritos na Lista de Componetes.
4. Seguir o Manual_de_Montagem_v4.pdf

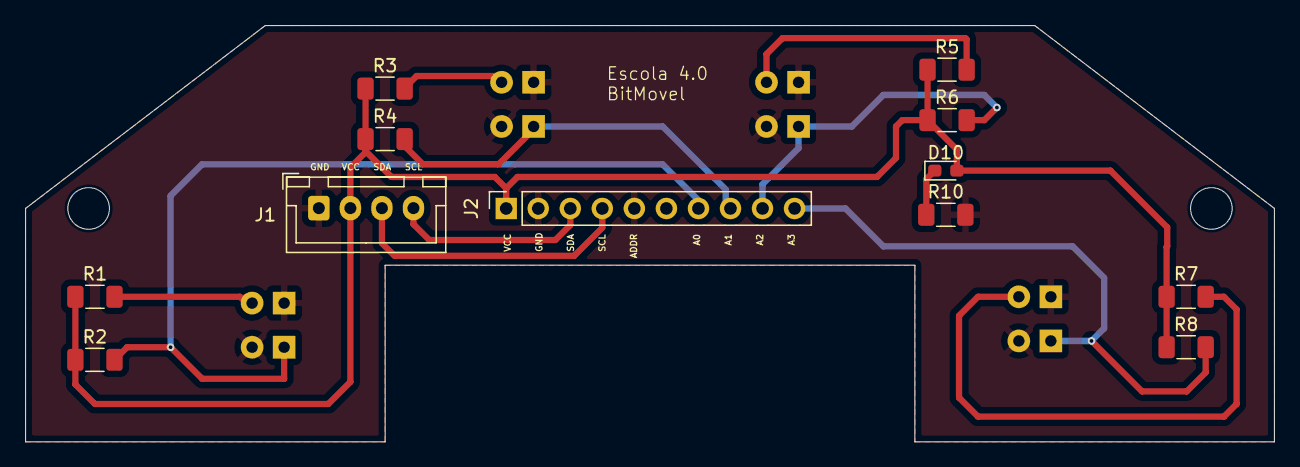
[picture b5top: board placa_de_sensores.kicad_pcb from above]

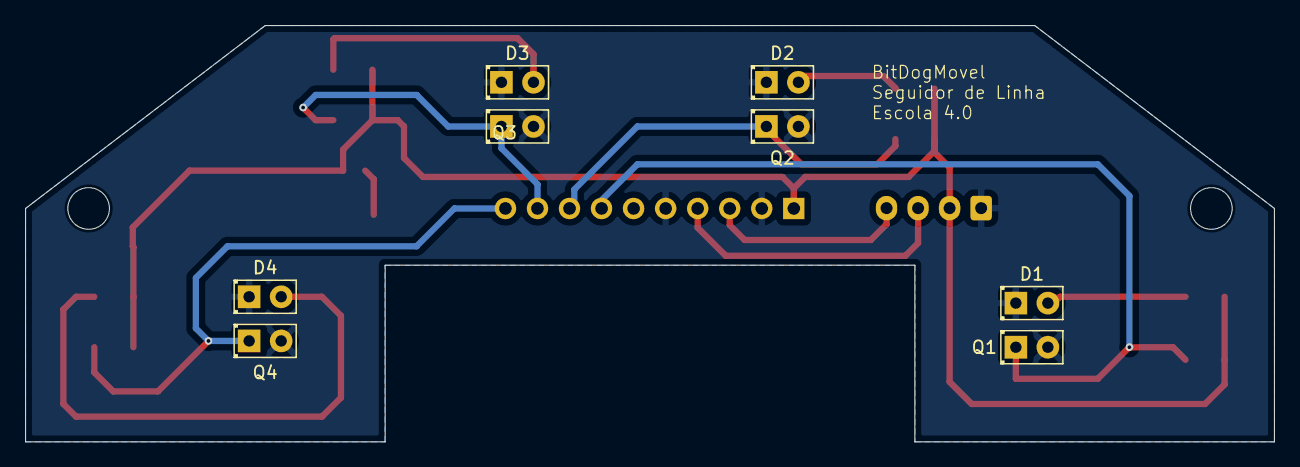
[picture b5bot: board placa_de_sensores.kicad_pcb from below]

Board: 2 copper layers, 99.0 x 33.0 mm, 20 parts (8 on the bottom side), 13 nets.

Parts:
D1, D2, D3, D4: Emissor; LED_D2.0mm_W4.8mm_H2.5mm_FlatTop
D10: LED; LED_0603_1608Metric_Pad1.05x0.95mm_HandSolder
J1: Conn_01x04_Pin; JST_XH_B4B-XH-A_1x04_P2.50mm_Vertical
J2: Conn_01x10_Socket; PinSocket_1x10_P2.54mm_Vertical
Q1, Q2, Q3, Q4: fototransistor; LED_D2.0mm_W4.8mm_H2.5mm_FlatTop
R1, R3, R5, R7: 300R; R_1206_3216Metric_Pad1.30x1.75mm_HandSolder
R2, R4, R6, R8: 10000R; R_1206_3216Metric_Pad1.30x1.75mm_HandSolder
R10: 1000R; R_1206_3216Metric_Pad1.30x1.75mm_HandSolder

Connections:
GND: D1.1 (K), D2.1 (K), D3.1 (K), D4.1 (K), J1.1, J2.2, J2.5, Q1.2 (E), Q2.2 (E), Q3.2 (E), Q4.2 (E), R10.2
unnamed: D1.2 (A), R1.2
unnamed: D2.2 (A), R3.2
unnamed: D3.2 (A), R5.2
unnamed: D4.2 (A), R7.2
unnamed: D10.1 (K), R10.1
VCC: D10.2 (A), J1.2, J2.1, R1.1, R2.1, R3.1, R4.1, R5.1, R6.1, R7.1, R8.1
out01: J2.7, Q1.1 (C), R2.2
out02: J2.8, Q2.1 (C), R4.2
out03: J2.9, Q3.1 (C), R6.2
out04: J2.10, Q4.1 (C), R8.2
sda: J1.3, J2.4
sdl: J1.4, J2.3

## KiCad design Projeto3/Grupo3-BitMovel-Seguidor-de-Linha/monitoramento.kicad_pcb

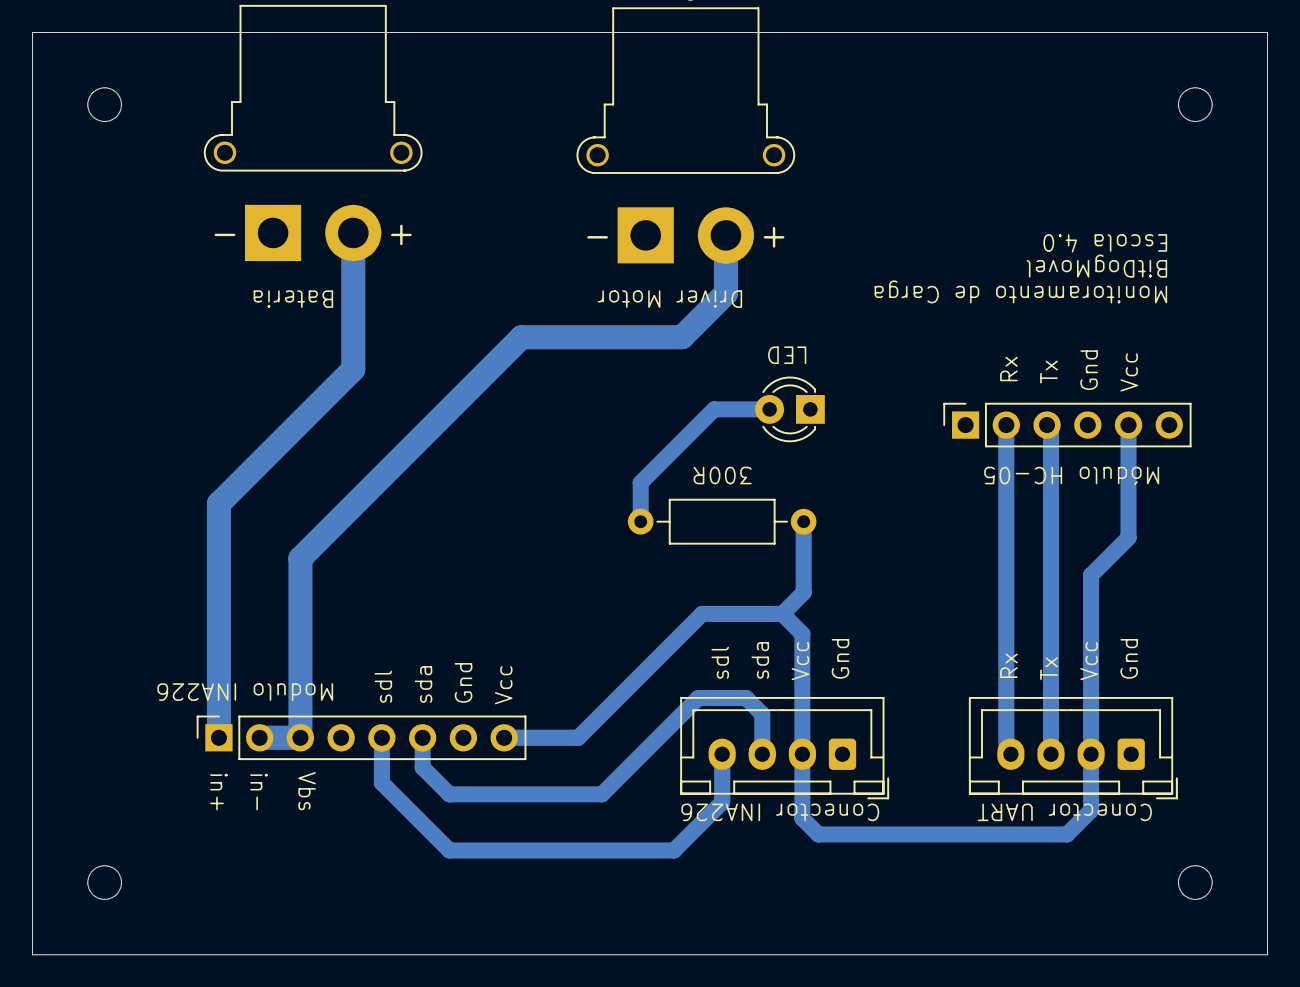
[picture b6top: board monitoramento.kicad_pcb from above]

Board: 2 copper layers, 77.0 x 57.5 mm, 8 parts (0 on the bottom side), 9 nets.

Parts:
Bateria1: Screw_Terminal_01x02; AMASS_XT30PW-F_1x02_P2.50mm_Horizontal
Carga1: Screw_Terminal_01x02; AMASS_XT30PW-F_1x02_P2.50mm_Horizontal
ConectorINA226: Conn_01x04_Pin; JST_XH_B4B-XH-A_1x04_P2.50mm_Vertical
Conector_Uart1: Conn_01x04_Pin; JST_XH_B4B-XH-A_1x04_P2.50mm_Vertical
D1: LED; LED_D3.0mm
HC5: Conn_01x06_Socket; PinSocket_1x06_P2.54mm_Vertical
Modulo_INA226: Conn_01x08_Socket; PinSocket_1x08_P2.54mm_Vertical
R1: 300R; R_Axial_DIN0207_L6.3mm_D2.5mm_P10.16mm_Horizontal

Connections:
GND: Bateria1.1, Carga1.1, ConectorINA226.1, Conector_Uart1.1, D1.1 (K), HC5.4, Modulo_INA226.7
unnamed: Bateria1.2, Modulo_INA226.1
unnamed: Carga1.2, Modulo_INA226.2, Modulo_INA226.3
unnamed: D1.2 (A), R1.2
Rx: Conector_Uart1.4, HC5.2
Tx: Conector_Uart1.3, HC5.3
VCC: ConectorINA226.2, Conector_Uart1.2, HC5.5, Modulo_INA226.8, R1.1
sda: ConectorINA226.3, Modulo_INA226.6
sdl: ConectorINA226.4, Modulo_INA226.5

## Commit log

2024-08-20 arquivo timer
2024-08-22 Adicionando o projeto do Grupo 5
    O projeto consiste na comparação entre estratégias de temporização, utilizando delay ou timers.
2024-08-24 Adiciona o modo timer
    Foi implementado o uso de timer para comparação direta com delay. Também foi adicionada uma função para troca do estado do LED.
2024-08-26 Adição de versão inicial do README
2024-08-26 Adicionada pasta e Readme
2024-08-26 menus de seleção de questão e alternativa
2024-08-28 Adiciona botão B e imagem para oLED
    Adiciona a contagem de vezes que o botão B foi pressionado também e nova imagem para exibição no display oLED, mas ainda não houve sua implementação durante uma rotina.
2024-08-29 Adiciona novo estado no modo delay e atualização do README
2024-08-30 Adiciona comentários no código e muda nomes de variáveis e funções para português para facilitar explicações para alunos
2024-08-31 Finaliza a documentação do código e amplia o README
2024-09-01 Colocando pasta com codigo e readme
    coloca código main e reame
2024-09-01 Adiciona
    Adicionei conteudo no readme e coloquei o novos ficheiro como documento do tecnico e do usuario
2024-09-01 actualização
2024-09-01 atualização dos documentos
2024-09-01 Add files via upload
    Carga de imagen do fluxograma requerida
2024-09-01 Update README.md
    Inclusão da imagen dos fluxogramas
2024-09-01 Atualizar o Documento do usuário.txt
2024-09-01 Atualizar o Documento técnico.txt
2024-09-01 Atualiza o README
2024-09-01 Update readme.md
    Pequenas correções e ajustes realizadas.
2024-09-01 Update Documento do usuário.txt
    Correções e melhoria do texto.
2024-09-01 Update readme.md
    Descrição das cores possíveis
2024-09-02 Update readme.md
    Formatar de forma mais dinâmica a visualização.
2024-09-02 Display Oled e Matriz RGB
2024-09-02 Update main.py
    Atualiza a animação da seta na matriz de leds
2024-09-02 Add files via upload
    Adiciona slides do material para aula
2024-09-02 Atualizar o readme.md
2024-09-02 gamedoglab
2024-09-02 adicionando_readme.md
2024-09-02 codigo_projeto01.py
2024-09-02 pergunta_resposta.py
2024-09-02 Rename projeto01.py to main.py
2024-09-02 Adicionando imagem fluxograma
2024-09-02 Remove código comentado e aumenta tempo de timer
2024-09-02 Add files via upload
    Adiciona exemplos ou problemas para resolver no material da aula
2024-09-10 Add files via upload
    Codigos MPU6050 acelerometro
2024-09-28 projetos
2024-09-28 adicao de readme
2024-09-28 ajuste no readme
2024-09-29 atualizacao readme
2024-09-29 Adiciona repositório do projeto do Grupo 5
2024-09-29 batalha naval
2024-09-29 espaçamento
2024-09-29 cameleão
2024-09-29 Corrige comentários do código
2024-09-29 Adiciona fluxogramas
2024-09-29 camaleão
2024-09-29 Adiciona QR Code para download do aplicativo
2024-09-29 Rename fluxograma.pdf to Projeto 2 - Grupo 4 _fluxograma.pdf
2024-09-29 Rename readme.md to Projeto 2 - Grupo 4 _readme.md
2024-09-29 Rename sensor_cor01.py to Projeto 2 - Grupo 4 _sensor_cor01.py
2024-09-29 Rename Projeto 2 - Grupo 4 _sensor_cor01.py to sensor_cor01.py
2024-09-29 Edita o README e adiciona imagens com fundo branco
2024-09-29 Adiciona os materiais para a aula recomendada
2024-09-29 inclusao pecas impressao 3d
2024-09-29 Subindo o código do projeto
2024-09-29 Adição do projeto do aplicativo de celular
2024-09-29 readme: correcao link relatorio
2024-09-30 correcao readme e adicao fluxograma
2024-09-30 fluxograma, mudanca pdf para png
2024-10-01 Atualiza arquivos após mudança de nome do app
2024-10-01 Remove espaço após QR Code
2024-10-01 Corrige lista do README
2024-10-01 Apresentação
2024-10-01 Apresentação slides
2024-10-01 adicao robo virtual e correcao do passo a passo de execucao
2024-10-27 modulo i2d
2024-10-27 Pasta para entrega do Projeto 3
2024-11-01 Adiciona projeto do aplicativo de celular, código da ESP32-CAM e código da RPi Pico para controle do BitMóvel
2024-11-01 Adiciona comentários no trecho de detecção de objetos
2024-11-03 Adiciona README e imagens, atualiza comentários do código da ESP32-CAM
2024-11-04 Atualização do README
2024-11-10 Adiciona manual de uso do robô explorador
2024-11-11 Adiciona PCI ao projeto do BitMóvel
2024-11-11 Tenta corrigir tabela do README
2024-11-11 Corrige tabela do README
2024-11-11 Adiciona apresentação preliminar
    Adiciona apresentação preliminar do projeto
2024-11-12 Atualiza o fluxograma do código rodando na BitDogLab
2024-11-12 Atualiza apresentação
2024-11-12 Update main.py
    Atualiza leitura de sensores e teste de servo motores
2024-11-12 Atualiza apresentação
    Atualiza apresentação com propostas para aula
2024-11-17 readme.md
    ewe
2024-11-17 readme
2024-11-17 imagem
2024-11-17 Altera código de recebimento de comandos via Bluetooth para controlar servo motores
2024-11-17 Atualiza o aplicativo do BitMovel Explorar para adicionar movimentação dos servo motores via joystick
2024-11-17 eliminação imagem
2024-11-18 Atualiza app do BitMóvel Explorador para adicionar tela com leitura do AHT10 e o código em python para enviar esses dados
    A tela de leitura do AHT10 é baseada na continuação do projeto https://github.com/danielvieira95/Projetos_Disciplina_IE323/tree/main/Projeto2/Grupo2-Projeto2-EfeitoEstufa, do aluno Victor Anthony Tei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
2024-11-18 Transforma int em bytes para transmissão via UART
2024-11-18 Atualiza README do BitDogMóvel Explorador
2024-11-19 Corrige envio de bytes via Bluetooth e movimentação dos servo motores
2024-11-19 Atualiza README do BitMovel Explorador
2024-11-21 Atualiza projeto do aplicativo do BitMóvel Explorador feito no App Inventor
2024-11-21 commit inicial de documentacao
2024-11-22 Adiciona o aplicativo no formato apk e revisão do README
2024-11-22 docs
2024-11-23 Atualiza fluxogramas do BitMóvel Explorador
2024-11-25 projeto 3 grupo 1
2024-11-26 Correção BitDogStore
2024-11-26 Atualização Instaladores BitDogStore
2024-11-26 Código_do_Projeto
    Subindo o código do projeto para o github
2024-11-26 Aplicativo
    Subindo o aplicativo do projeto
2024-11-26 App.md
    Apenas adicionei o funcionamento do app e como rodar o código no arudino
2024-11-27 Subindo_placas_eletronica
2024-11-27 Create Placas eletrônicas
2024-11-27 Create arquivo
2024-11-28 Atualiza aplicativo de celular e main.py para versão funcional do sensor de temperatura do BitMovel Explorador
2024-11-28 Atualiza TODO list do BitMovel Explorador
2024-11-29 Atualiza README do BitMovel Explorador com novas instruções e imagens para explicar instruções
2024-11-29 Atualiza arquivo PDF do manual simplificado do BitMovel Explorador
2024-11-29 Adiciona image para exemplificar processo do BitMóvel Explorador
2024-11-30 Atualiza manual simplificado do BitMovel Explorador com imagem
2024-11-30 atualização imagens e main e bibliotecas
2024-11-30 Adiciona tabela com componentes do BitMovel Explorador
2024-11-30 Adição de recomendações com bateria do BitMovel Explorador
2024-12-01 tutorial-disolay TFT
2024-12-02 Referencia as imagens das instruções do BitMovel Explorador
2024-12-03 Remove seção TODO do README do BitMóvel Explorador
2024-12-03 inclusao desenho 3d fabricacao
2024-12-03 upload figs compara proj2 e proj3
2024-12-03 Update README.md
    inclusao imagens
2024-12-03 Update README.md
    corrigido png para jpeg
2024-12-03 adicao e organizacao de imagens
2024-12-03 pasta imagens
2024-12-03 Update README.md
    adicao imagens readme
2024-12-03 Update README.md
    correcao formato extensao imagens
2024-12-03 Update README.md
    coreccao extensao imagens
2024-12-03 Update README.md
    intrucoes de fabricacao
2024-12-07 Rename Manual do professor (Projeto 3 - Grupo 4).pdf to Manual do professor
2024-12-07 Rename Projeto 3 - Grupo 4 _Fluxograma do projeto (Atualizado).pdf to Fluxograma da aplicação
2025-01-27 Corrige QR Code para download do aplicativo de celular do robô explorador
